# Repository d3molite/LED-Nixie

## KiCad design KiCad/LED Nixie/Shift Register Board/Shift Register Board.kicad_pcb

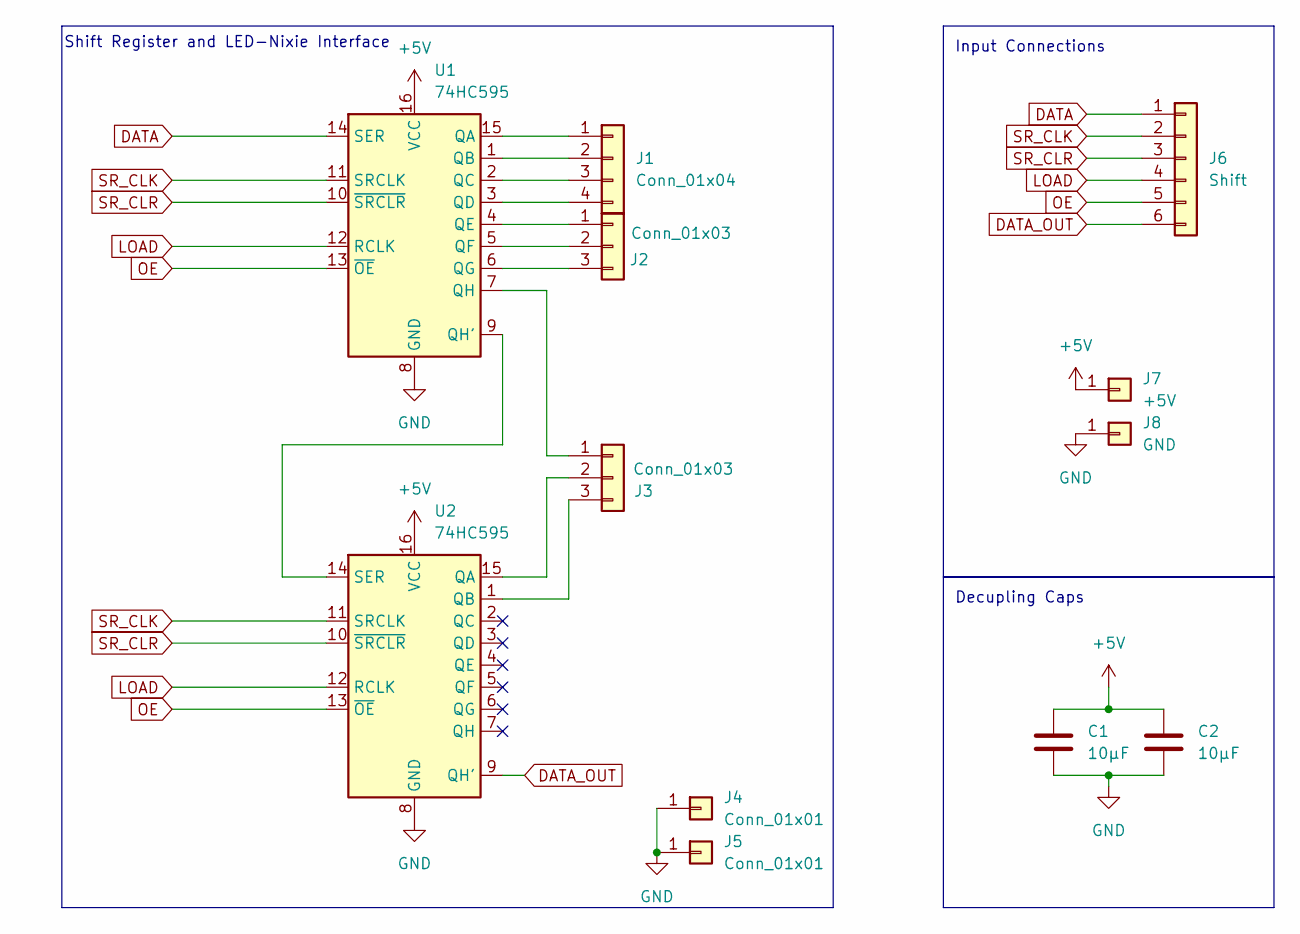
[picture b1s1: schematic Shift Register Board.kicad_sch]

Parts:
C1, C2: 10µF; C_0805_2012Metric
J1: Conn_01x04; PinSocket_1x04_P2.00mm_Vertical
J2, J3: Conn_01x03; PinSocket_1x03_P2.00mm_Vertical
J4, J5: Conn_01x01; PinSocket_1x01_P2.00mm_Vertical
J6: Shift; PinHeader_1x06_P2.54mm_Vertical
J7: +5V; PinHeader_1x01_P2.54mm_Vertical
J8: GND; PinHeader_1x01_P2.54mm_Vertical
U1, U2: 74HC595; SO-16_3.9x9.9mm_P1.27mm

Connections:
+5V: C1.1, C2.1, J7.1, U1.16 (VCC), U2.16 (VCC)
DATA: J6.1, U1.14 (SER)
DATA_OUT: J6.6, U2.9 (QH')
GND: C1.2, C2.2, J4.1, J5.1, J8.1, U1.8 (GND), U2.8 (GND)
LOAD: J6.4, U1.12 (RCLK), U2.12 (RCLK)
unnamed: J1.1, U1.15 (QA)
unnamed: J1.2, U1.1 (QB)
unnamed: J1.3, U1.2 (QC)
unnamed: J1.4, U1.3 (QD)
unnamed: J2.1, U1.4 (QE)
unnamed: J2.2, U1.5 (QF)
unnamed: J2.3, U1.6 (QG)
unnamed: J3.1, U1.7 (QH)
unnamed: J3.2, U2.15 (QA)
unnamed: J3.3, U2.1 (QB)
unnamed: U1.9 (QH'), U2.14 (SER)
OE: J6.5, U1.13 (~OE), U2.13 (~OE)
SR_CLK: J6.2, U1.11 (SRCLK), U2.11 (SRCLK)
SR_CLR: J6.3, U1.10 (~SRCLR), U2.10 (~SRCLR)

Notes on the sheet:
Input Connections
Decupling Caps
Shift Register and LED-Nixie Interface

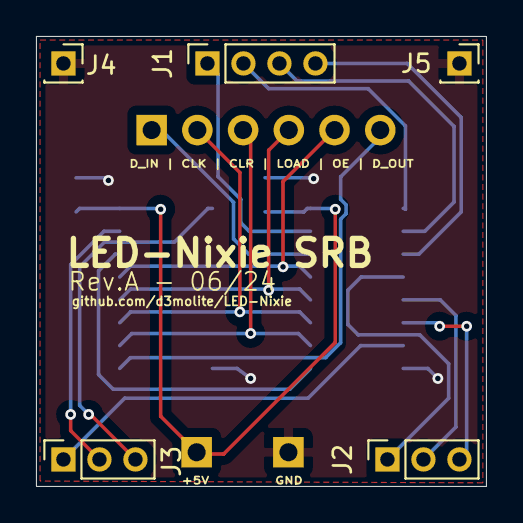
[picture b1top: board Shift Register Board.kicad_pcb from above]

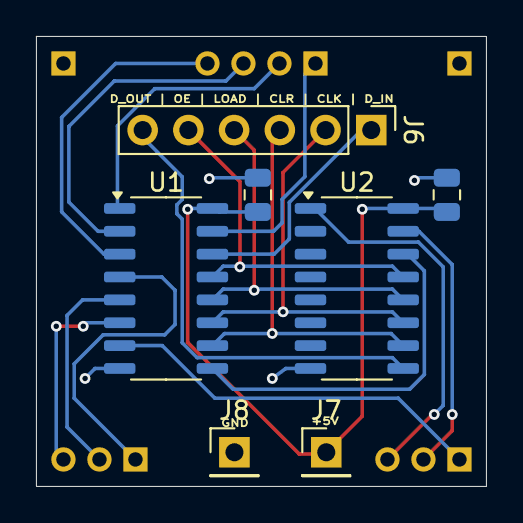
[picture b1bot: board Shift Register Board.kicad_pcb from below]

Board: 2 copper layers, 25.0 x 25.0 mm, 12 parts (7 on the bottom side), 19 nets.

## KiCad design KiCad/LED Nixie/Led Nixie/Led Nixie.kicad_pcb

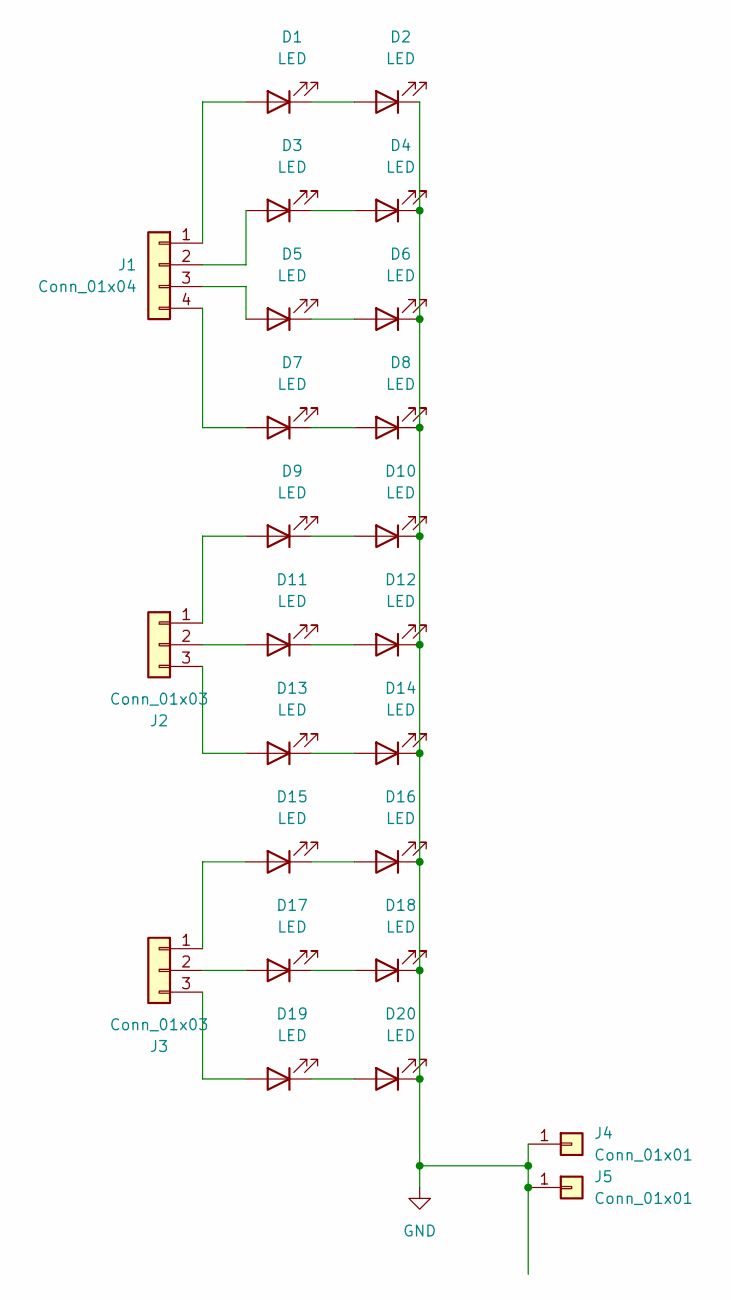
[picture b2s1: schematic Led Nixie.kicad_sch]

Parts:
D1, D2, D3, D4, D5, D6, D7, D8, D9, D10, D11, D12, D13, D14, D15, D16, D17, D18, D19, D20: LED; LED_1206_3216Metric_nosilkscreen
J1: Conn_01x04; PinHeader_1x04_P2.00mm_Vertical
J2, J3: Conn_01x03; PinHeader_1x03_P2.00mm_Vertical
J4, J5: Conn_01x01; PinHeader_1x01_P2.00mm_Vertical

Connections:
GND: D2.1 (K), D4.1 (K), D6.1 (K), D8.1 (K), D10.1 (K), D12.1 (K), D14.1 (K), D16.1 (K), D18.1 (K), D20.1 (K), J4.1, J5.1
unnamed: D1.2 (A), J1.1
unnamed: D1.1 (K), D2.2 (A)
unnamed: D3.2 (A), J1.2
unnamed: D3.1 (K), D4.2 (A)
unnamed: D5.2 (A), J1.3
unnamed: D5.1 (K), D6.2 (A)
unnamed: D7.2 (A), J1.4
unnamed: D7.1 (K), D8.2 (A)
unnamed: D9.2 (A), J2.1
unnamed: D9.1 (K), D10.2 (A)
unnamed: D11.2 (A), J2.2
unnamed: D11.1 (K), D12.2 (A)
unnamed: D13.2 (A), J2.3
unnamed: D13.1 (K), D14.2 (A)
unnamed: D15.2 (A), J3.1
unnamed: D15.1 (K), D16.2 (A)
unnamed: D17.2 (A), J3.2
unnamed: D17.1 (K), D18.2 (A)
unnamed: D19.2 (A), J3.3
unnamed: D19.1 (K), D20.2 (A)

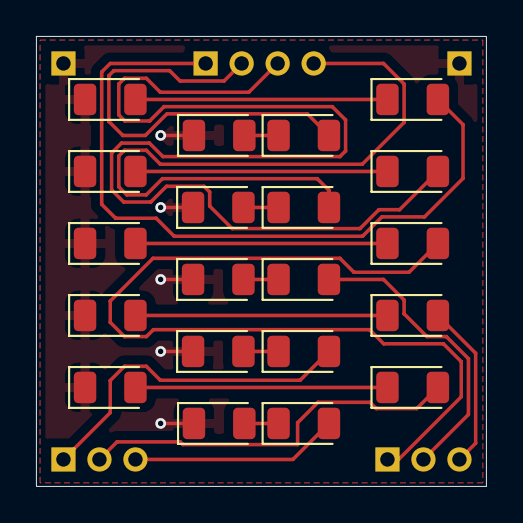
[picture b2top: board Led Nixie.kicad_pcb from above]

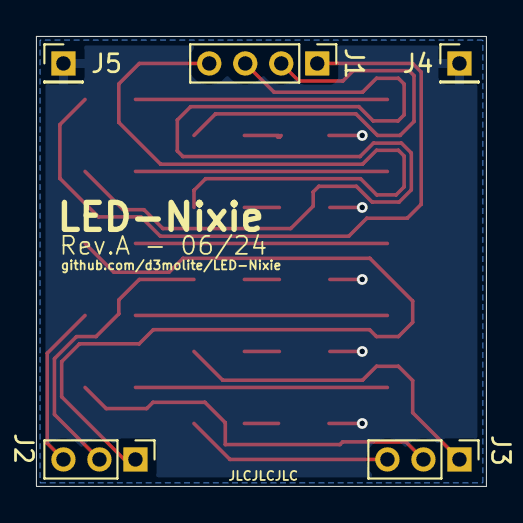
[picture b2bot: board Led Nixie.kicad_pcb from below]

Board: 2 copper layers, 25.0 x 25.0 mm, 25 parts (5 on the bottom side), 21 nets.

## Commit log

2024-07-09 Added KiCad Project
2024-07-12 Updated Nixie-PCB
2024-07-12 Demo-Sketch
    Shift Out
2024-07-13 updated PCB
2024-07-13 added Decupling Caps
2024-07-13 Fix DRU-Errors
